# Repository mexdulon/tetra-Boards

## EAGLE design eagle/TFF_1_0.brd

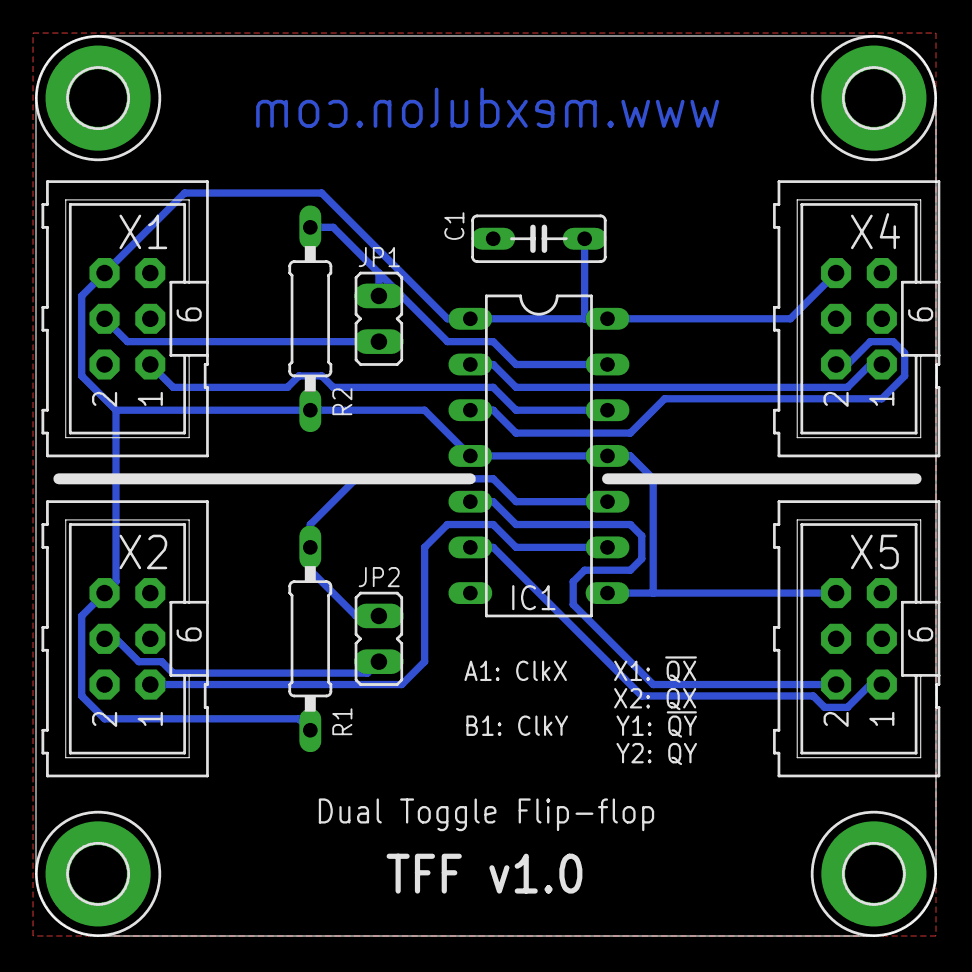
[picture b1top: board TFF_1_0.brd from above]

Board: 2 copper layers, 50.0 x 50.0 mm, 14 parts (0 on the bottom side), 12 nets.

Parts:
C1: 100n; C050-025X075
H1, H2, H3, H4: MOUNT-PAD-ROUND3.2; 3,2-PAD
IC1: 74HC107N; DIL14
JP1: !ClrX! A4; JP1
JP2: !ClrY! B4; JP1
R1, R2: 1k; 0207/10
X1: In A; ML-6
X2: In B; ML-6
X4: Out X; ML-6
X5: Out Y; ML-6

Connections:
GND: C1.2, H1.B3,2, H2.B3,2, H3.B3,2, H4.B3,2, IC1.7, X1.5, X2.5, X4.5, X5.5
unnamed: IC1.13, JP1.2, R2.2
unnamed: JP1.1, X1.4
unnamed: JP2.1, X2.4
unnamed: IC1.10, JP2.2, R1.2
unnamed: IC1.9, X2.1
unnamed: IC1.12, X1.1
unnamed: IC1.2, X4.1
unnamed: IC1.3, X4.2
unnamed: IC1.6, X5.1
unnamed: IC1.5, X5.2
VCC: C1.1, IC1.1, IC1.4, IC1.8, IC1.11, IC1.14, R1.1, R2.1, X1.6, X2.6, X4.6, X5.6

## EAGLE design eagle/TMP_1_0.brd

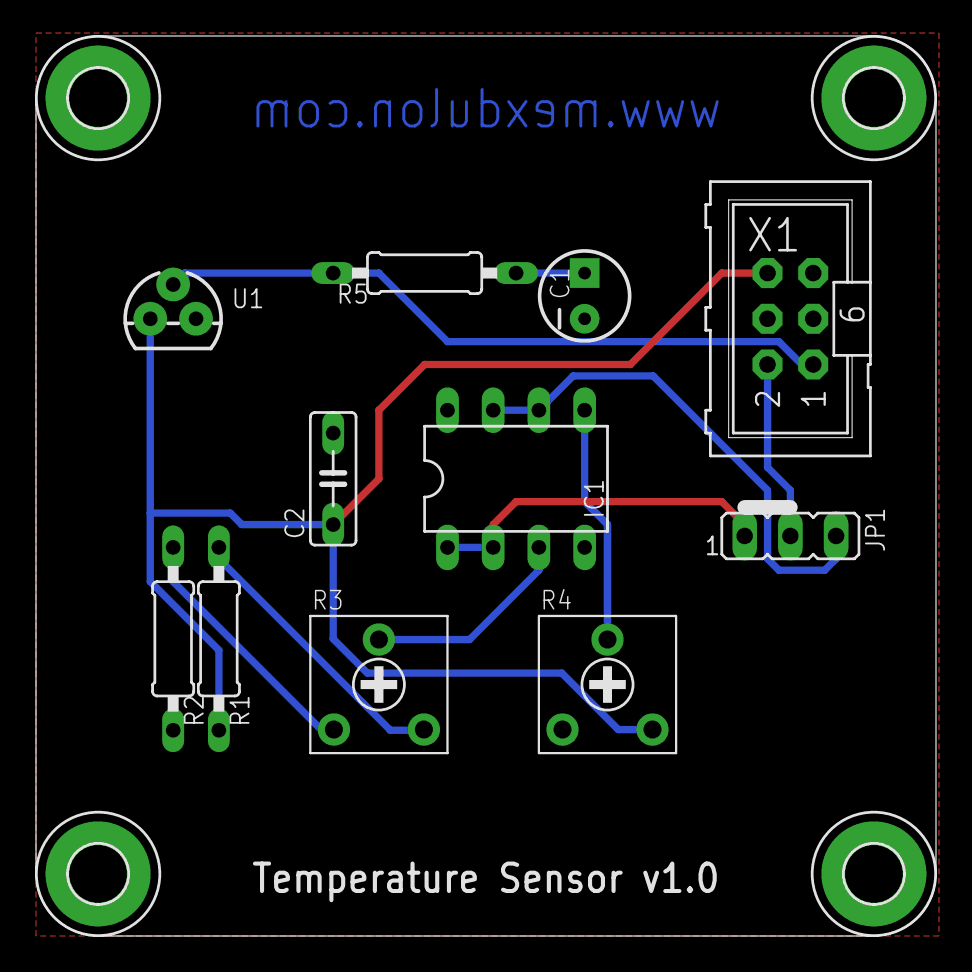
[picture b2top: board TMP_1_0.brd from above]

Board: 2 copper layers, 50.0 x 50.0 mm, 15 parts (0 on the bottom side), 11 nets.

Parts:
C1: 1u; CPOL-RADIAL-10UF-25V
C2: 100n; C050-025X075
H1, H2, H3, H4: MOUNT-PAD-ROUND3.2; 3,2-PAD
IC1: LM358N; DIL08
JP1: Ref A/B; JP2-U
R1, R2: 10k; 0207/10
R3: 1k; ACP-6L
R4: 10k; ACP-6L
R5: 75R; 0207/10
U1: LM35; TO-92
X1: Out~; ML-6

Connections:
GND: C1.2, C2.2, H1.B3,2, H2.B3,2, H3.B3,2, H4.B3,2, R2.1, R4.1, U1.3, X1.5
unnamed: R2.2, R3.1
unnamed: R1.1, R3.3
unnamed: IC1.3, R3.2
unnamed: IC1.1, IC1.2, JP1.1
unnamed: JP1.2, X1.2
unnamed: IC1.6, IC1.7, JP1.3
unnamed: R5.2, U1.2, X1.1
unnamed: IC1.5, R4.2
unnamed: C1.1, R5.1
VCC: C2.1, R1.2, R4.3, U1.1, X1.6

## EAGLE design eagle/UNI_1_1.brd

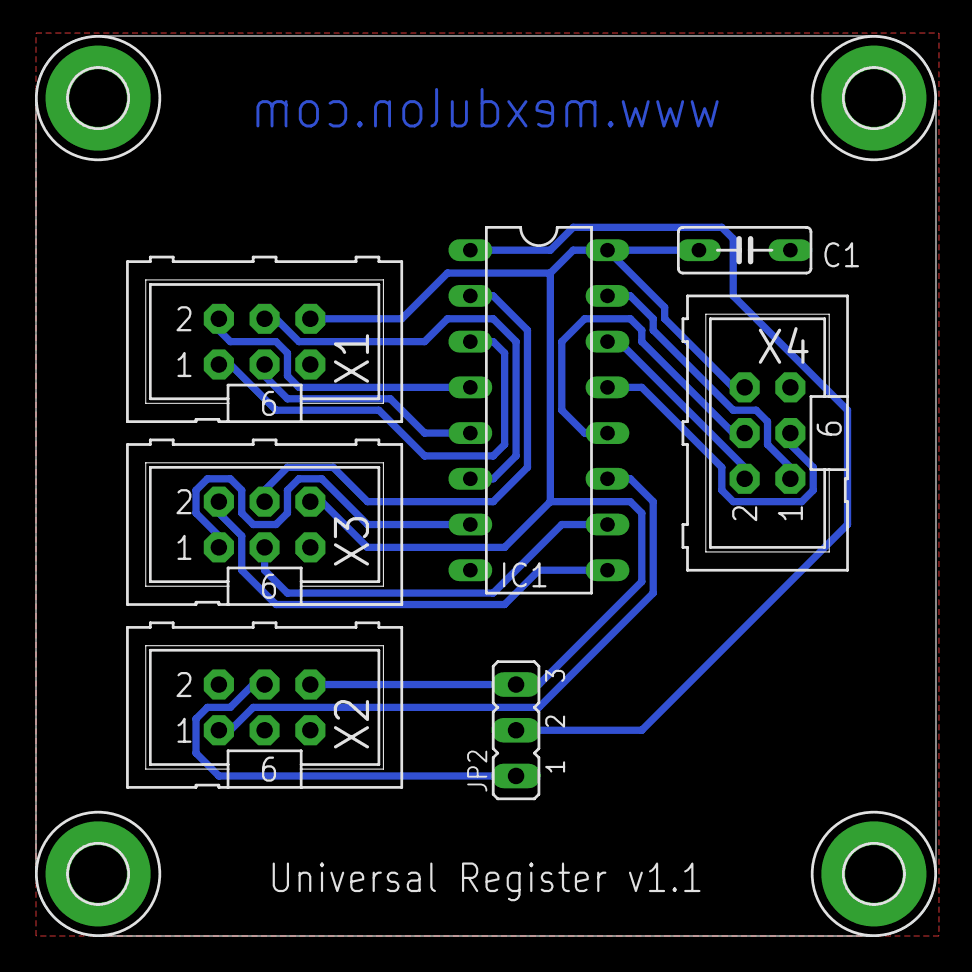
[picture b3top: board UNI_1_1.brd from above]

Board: 2 copper layers, 50.0 x 50.0 mm, 11 parts (0 on the bottom side), 17 nets.

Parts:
C1: 100n; C050-025X075
H1, H2, H3, H4: MOUNT-PAD-ROUND3.2; 3,2-PAD
IC1: 74HC194N; DIL16
JP2: /CLR 4/H; JP2
X1: In; ML-6
X2: Ctrl; ML-6
X3: Mode; ML-6
X4: Out; ML-6

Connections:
GND: C1.2, H1.B3,2, H2.B3,2, H3.B3,2, H4.B3,2, IC1.8, X1.5, X2.5, X3.5, X4.5
unnamed: IC1.3, X1.1
unnamed: IC1.4, X1.2
unnamed: IC1.5, X1.3
unnamed: IC1.6, X1.4
unnamed: IC1.11, X2.1
unnamed: IC1.1, JP2.2
unnamed: IC1.15, X4.1
unnamed: IC1.14, X4.2
unnamed: IC1.13, X4.3
unnamed: IC1.12, X4.4
unnamed: IC1.9, X3.2
unnamed: IC1.2, X3.4
unnamed: JP2.1, X2.4
unnamed: IC1.10, X3.3
unnamed: IC1.7, X3.1
VCC: C1.1, IC1.16, JP2.3, X1.6, X2.6, X3.6, X4.6

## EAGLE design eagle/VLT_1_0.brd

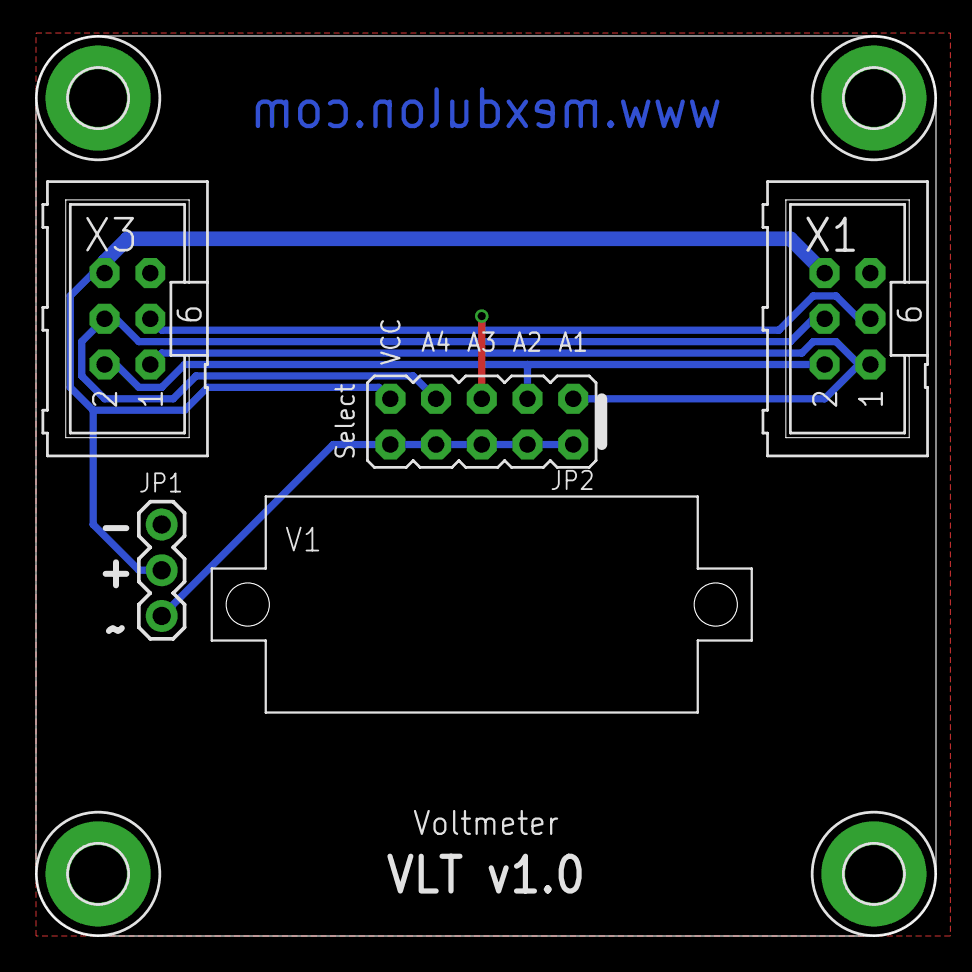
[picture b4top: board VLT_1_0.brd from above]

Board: 2 copper layers, 50.0 x 50.0 mm, 9 parts (0 on the bottom side), 7 nets.

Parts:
H1, H2, H3, H4: MOUNT-PAD-ROUND3.2; 3,2-PAD
JP1: 1X03
JP2: JP5Q
V1: VOLTMETER-28
X1: Out A~; ML-6
X3: In A~; ML-6

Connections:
GND: H1.B3,2, H2.B3,2, H3.B3,2, H4.B3,2, JP1.3, X1.5, X3.5
unnamed: JP2.1, X1.1, X3.1
unnamed: JP2.3, X1.2, X3.2
unnamed: JP2.5, X1.3, X3.3
unnamed: JP2.7, X1.4, X3.4
unnamed: JP1.1, JP2.2, JP2.4, JP2.6, JP2.8, JP2.10
VCC: JP1.2, JP2.9, X1.6, X3.6

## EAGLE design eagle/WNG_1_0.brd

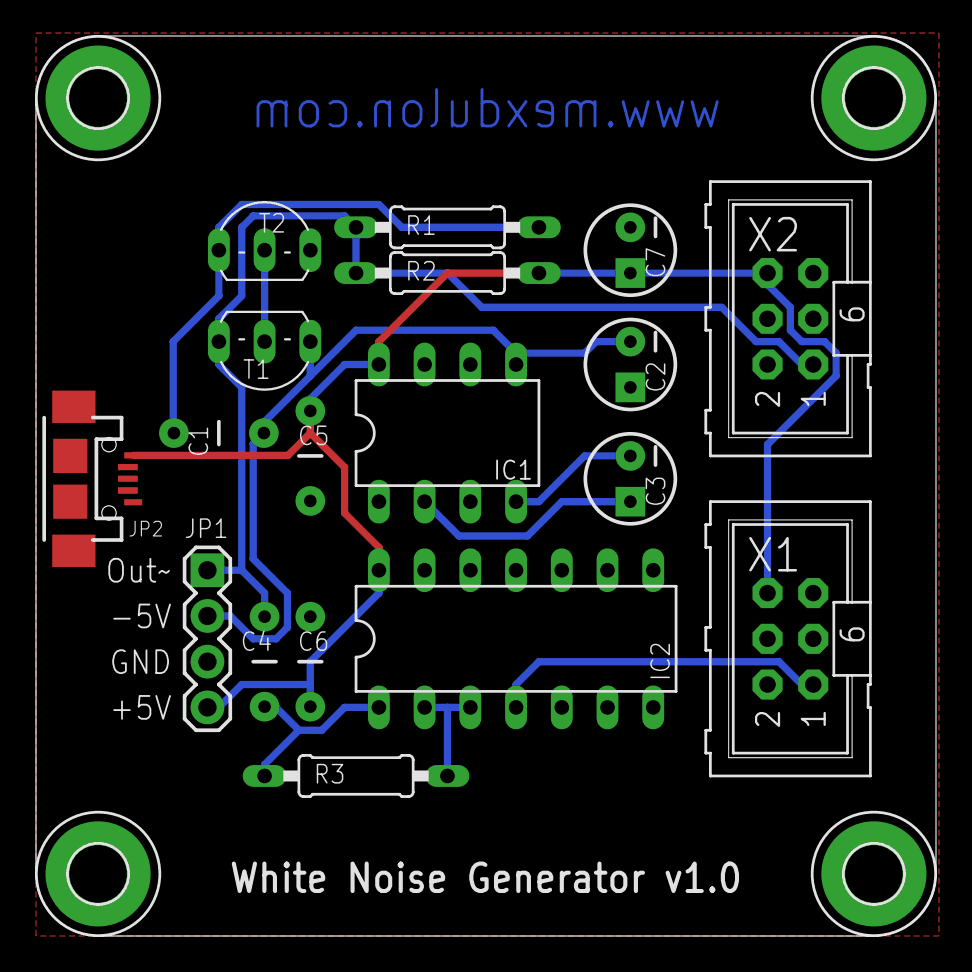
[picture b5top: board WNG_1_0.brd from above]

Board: 2 copper layers, 50.0 x 50.0 mm, 22 parts (0 on the bottom side), 11 nets.

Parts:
C1: 1u; CAP-PTH-5MM
C2, C3, C7: 10u; CPOL-RADIAL-10UF-25V
C4, C5, C6: 100n; CAP-PTH-5MM
H1, H2, H3, H4: MOUNT-PAD-ROUND3.2; 3,2-PAD
IC1: ICL7660; DIL08
IC2: 74HC04N; DIL14
JP1: Out; 1X04
JP2: USB-MICRO; USB-MICROB2
R1: 47k; 0207/10
R2: 4k7; 0207/10
R3: 1M; 0207/10
T1, T2: 2n3904; TO92-EBC
X1: Digital; ML-6
X2: Analog~; ML-6

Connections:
-5V: C1.2, C2.2, IC1.5, JP1.2, T1.E
GND: C2.1, C5.2, C6.2, C7.2, H1.B3,2, H2.B3,2, H3.B3,2, H4.B3,2, IC1.3, IC2.5, IC2.7, IC2.9, IC2.11, IC2.13, JP1.3, JP2.GND, JP2.MT1, JP2.MT2, X1.5, X2.5
unnamed: C1.1, R1.1, T2.E
unnamed: C4.2, IC2.1, R3.1
unnamed: C4.1, JP1.1, R1.2, R2.1, T1.C, X2.1
unnamed: T1.B, T2.B
unnamed: C3.1, IC1.2
unnamed: C3.2, IC1.4
unnamed: IC2.2, IC2.3, R3.2
unnamed: IC2.4, X1.1
VCC: C5.1, C6.1, C7.1, IC1.8, IC2.14, JP1.4, JP2.VBUS, R2.2, X1.6, X2.6

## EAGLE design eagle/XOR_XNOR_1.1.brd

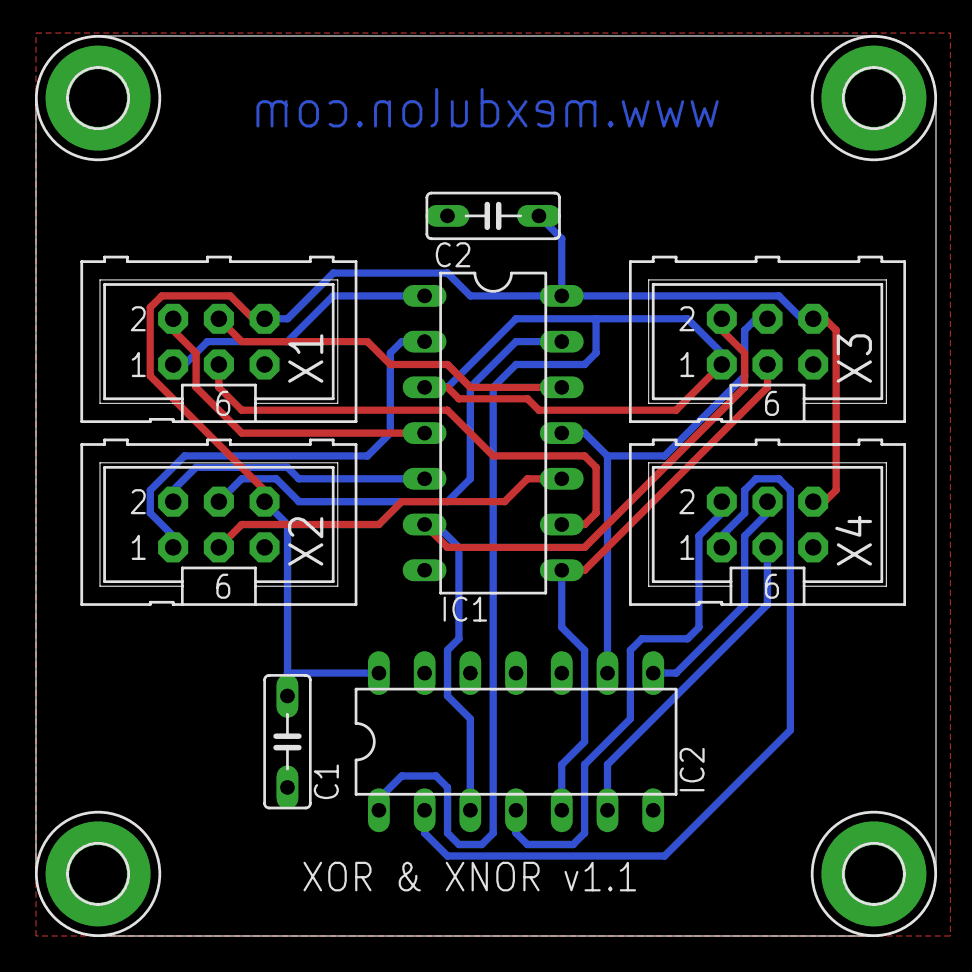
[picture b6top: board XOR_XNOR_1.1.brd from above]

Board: 2 copper layers, 50.0 x 50.0 mm, 12 parts (0 on the bottom side), 18 nets.

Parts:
C1, C2: 100n; C050-025X075
H1, H2, H3, H4: MOUNT-PAD-ROUND3.2; 3,2-PAD
IC1: 74HC86N; DIL14
IC2: 74HC04N; DIL14
X1: In A; ML-6
X2: In B; ML-6
X3: XOR; ML-6
X4: XNOR; ML-6

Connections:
GND: C1.2, C2.2, H1.B3,2, H2.B3,2, H3.B3,2, H4.B3,2, IC1.7, IC2.7, IC2.11, IC2.13, X1.5, X2.5, X3.5, X4.5
unnamed: IC1.3, IC2.1, X3.1
unnamed: IC1.6, IC2.3, X3.2
unnamed: IC1.8, IC2.5, X3.3
unnamed: IC1.11, IC2.9, X3.4
unnamed: IC2.2, X4.1
unnamed: IC2.4, X4.2
unnamed: IC2.6, X4.3
unnamed: IC2.8, X4.4
unnamed: IC1.1, X1.1
unnamed: IC1.2, X2.1
unnamed: IC1.5, X2.2
unnamed: IC1.4, X1.2
unnamed: IC1.9, X1.3
unnamed: IC1.10, X2.3
unnamed: IC1.12, X1.4
unnamed: IC1.13, X2.4
VCC: C1.1, C2.1, IC1.14, IC2.14, X1.6, X2.6, X3.6, X4.6

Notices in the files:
eagle/TFF_1_0.brd:
Licensed under CERN OHL v.1.2
parts and their libraries:
SparkFun-Sensors: Licensing: Creative Commons ShareAlike 4.0 International - https://creativecommons.org/licenses/by-sa/4.0
